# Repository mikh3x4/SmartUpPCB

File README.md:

this two may be needed to get submodule cloned

git submodule init
git submodule update

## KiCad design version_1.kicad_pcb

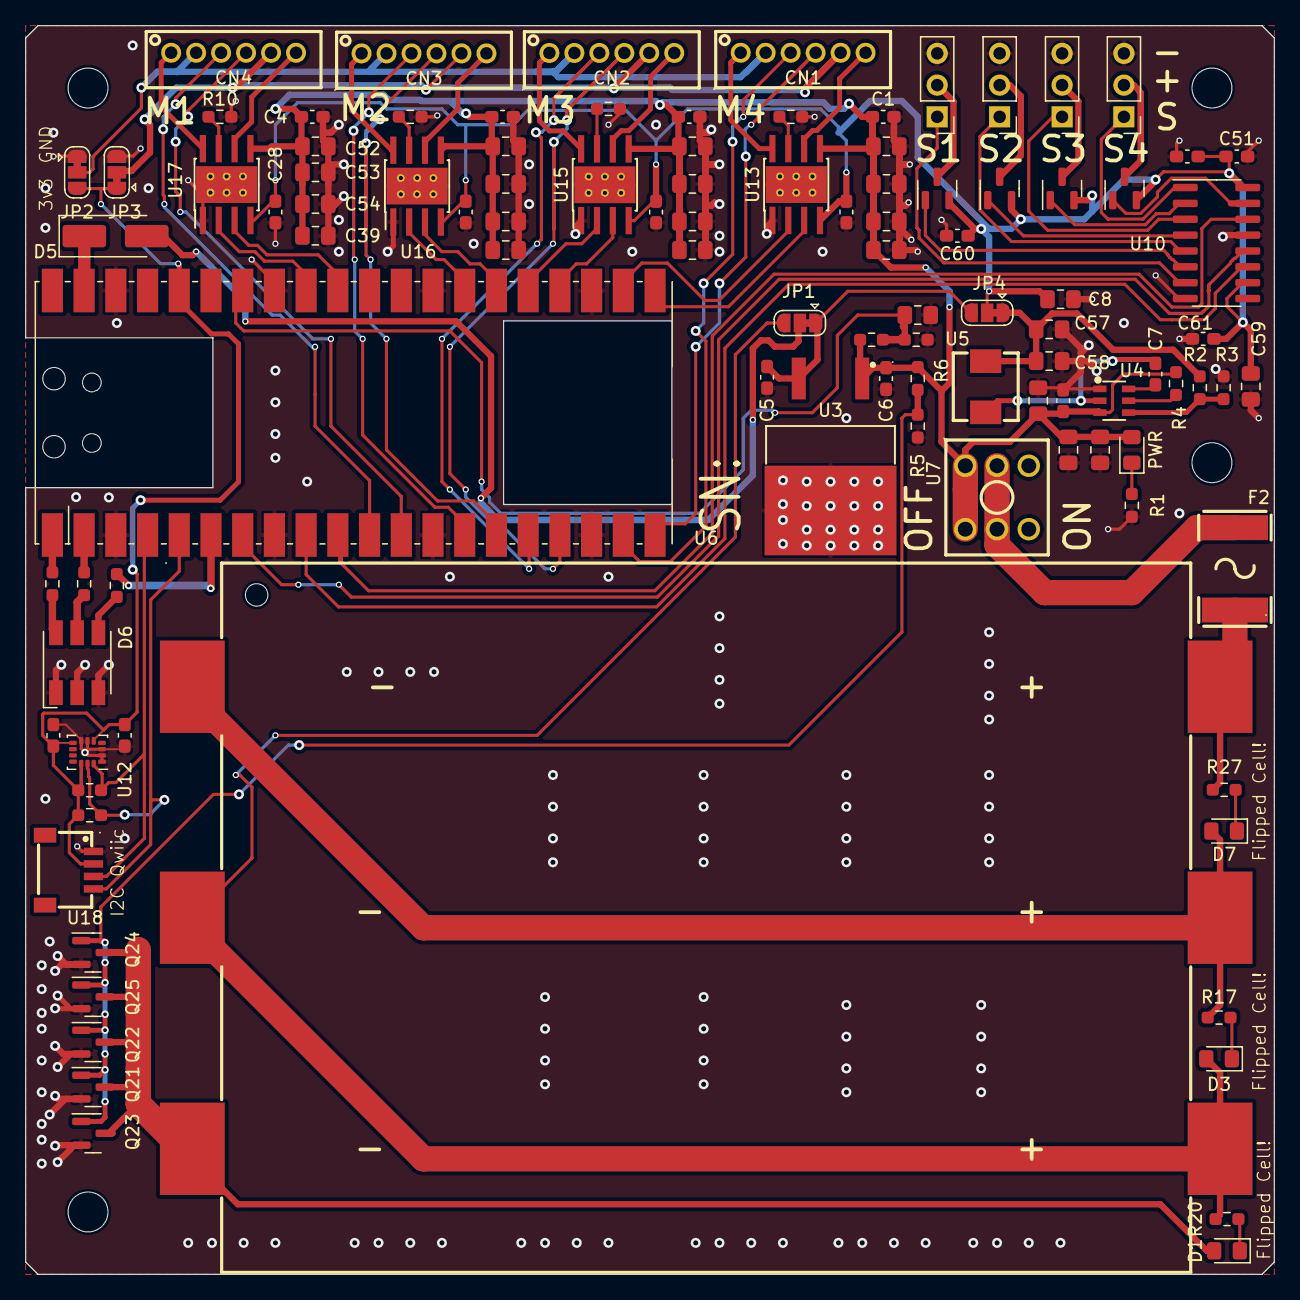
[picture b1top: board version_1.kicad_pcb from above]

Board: 4 copper layers, 100.0 x 100.0 mm, 107 parts (0 on the bottom side), 76 nets.

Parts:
C1, C2, C3, C4, C5, C7, C14, C16, C25, C26, C27, C28, C29, C50, C51, C60, C61: 100n; C_0603_1608Metric_Pad1.08x0.95mm_HandSolder
C6: 330n; C_0603_1608Metric_Pad1.08x0.95mm_HandSolder
C8, C11, C13, C15, C30, C31, C32, C33, C36, C37, C38, C39, C40, C41, C42, C45, C46, C47, C52, C53, C54, C57, C58, C59: 22u; C_0805_2012Metric_Pad1.18x1.45mm_HandSolder
CN1, CN2, CN3, CN4: B6B-PH-K-S(LF)(SN); CONN-TH_B6B-PH-K-S
D1, D3, D7: WRONG!; D_0805_2012Metric_Pad1.15x1.40mm_HandSolder
D4: PWR; D_0805_2012Metric_Pad1.15x1.40mm_HandSolder
D5: C145232; D_SMA_Handsoldering
D6: C2843868; LED_RGB_5050-6
F2: SMD2920B500TF; F2920
H1, H2, H3, H4: MountingHole; MountingHole_3.2mm_M3
JP1, JP2, JP3, JP4: Jumper_3_Bridged12; SolderJumper-3_P1.3mm_Bridged12_RoundedPad1.0x1.5mm
M5, M6, M7, M8: Motor_Servo_JR; PinHeader_1x03_P2.54mm_Vertical
Q17, Q18, Q19, Q20: AO3401A; SOT-23
Q21, Q22, Q23, Q24, Q25: AO3400A; SOT-23
R1, R21, R22, R23, R29, R30: 1k; R_0603_1608Metric_Pad0.98x0.95mm_HandSolder
R2: 56k; R_0603_1608Metric_Pad0.98x0.95mm_HandSolder
R3, R4, R25: 10k; R_0603_1608Metric_Pad0.98x0.95mm_HandSolder
R5, R6: 100k; R_0603_1608Metric_Pad0.98x0.95mm_HandSolder
R7, R8, R9, R10: 0.27; R_0603_1608Metric_Pad0.98x0.95mm_HandSolder
R17, R20, R27: 220; R_0603_1608Metric_Pad0.98x0.95mm_HandSolder
R26: 33k; R_0603_1608Metric_Pad0.98x0.95mm_HandSolder
U1: Pico; RPi_Pico_SMD_TH
U3: L7805CD2T-TR; TO-263-2_L10.0-W9.1-P5.08-LS15.2-TL
U4: TPS562209DDCR; SOT-23-6_L2.9-W1.6-P0.95-LS2.8-BL
U5: FXL0530-4R7-M; IND-SMD_L5.4-W5.2_FXL0530
U6: BH-18650-B5BA016; BAT-SMD_BH-18650-B5BA016
U7: 2AD1T1A2M2QES; SW-TH_2AD1T1A2M2QES
U10: 74HCT595D; SOP-16_3.9x9.9mm_P1.27mm
U12: C967633; LGA-14_3x2.5mm_P0.5mm_LayoutBorder3x4y
U13, U15, U16, U17: DRV8870DDA; Texas_HTSOP-8-1EP_3.9x4.9mm_P1.27mm_EP2.95x4.9mm_Mask2.4x3.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
U18: SM04B-SRSS-TB_(LF)(SN); CONN-SMD_4P-P1.00_SM04B-SRSS-TB-LF-SN

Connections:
1S: D3.2 (A), JP1.3 (B), R20.2, U6.3, U6.6
+3.3V: C16.1, C50.1, JP2.3 (B), JP3.1 (A), R29.1, R30.1, U1.36 (3V3), U12.5 (VDDIO), U12.8 (VDD), U12.12 (CS), U18.2
+5V: C8.1, C25.1, C26.1, C27.1, C28.1, C29.1, C51.1, C59.1, C60.1, C61.1, JP4.2 (C), Q17.2 (S), Q18.2 (S), Q19.2 (S), Q20.2 (S), U10.10 (~SRCLR), U10.16 (VCC), U13.4 (VREF), U15.4 (VREF), U16.4 (VREF), U17.4 (VREF)
/ENCODER1: CN1.3, U1.19 (GPIO14)
/ENCODER2: CN1.4, U1.20 (GPIO15)
/ENCODER3: CN2.3, U1.16 (GPIO12)
/ENCODER4: CN2.4, U1.17 (GPIO13)
/ENCODER5: CN3.3, U1.14 (GPIO10)
/ENCODER6: CN3.4, U1.15 (GPIO11)
/ENCODER7: CN4.3, U1.11 (GPIO8)
/ENCODER8: CN4.4, U1.12 (GPIO9)
/ML1: U1.21 (GPIO16), U13.3 (IN1)
/ML2: U1.24 (GPIO18), U15.3 (IN1)
/ML3: U1.26 (GPIO20), U16.3 (IN1)
/ML4: U1.31 (GPIO26_ADC0), U17.3 (IN1)
/MR1: U1.22 (GPIO17), U13.2 (IN2)
/MR2: U1.25 (GPIO19), U15.2 (IN2)
/MR3: U1.27 (GPIO21), U16.2 (IN2)
/MR4: U1.32 (GPIO27_ADC1), U17.2 (IN2)
/PWM_CLK: U1.9 (GPIO6), U10.11 (SRCLK)
/PWM_CS: U1.7 (GPIO5), U10.12 (RCLK)
/PWM_DATA: U1.10 (GPIO7), U10.14 (SER)
/SCL: R30.2, U1.5 (GPIO3), U12.13 (SCL), U18.4
/SDA: R29.2, U1.4 (GPIO2), U12.14 (SDA), U18.3
/Servo2/PWM: M7.1 (PWM), U10.3 (QD)
/Servo2/PWR: Q19.1 (G), U10.2 (QC)
/Servo/PWM: M8.1 (PWM), U10.1 (QB)
/Servo/PWR: Q20.1 (G), U10.15 (QA)
/Untitled Sheet4/PWM: M6.1 (PWM), U10.5 (QF)
/Untitled Sheet4/PWR: Q18.1 (G), U10.4 (QE)
/Untitled Sheet7/PWM: M5.1 (PWM), U10.7 (QH)
/Untitled Sheet7/PWR: Q17.1 (G), U10.6 (QG)
ENC_PWR_G: CN1.2, CN2.2, CN3.2, CN4.2, JP2.2 (C)
ENC_PWR_P: CN1.5, CN2.5, CN3.5, CN4.5, JP3.2 (C)
GND: C1.2, C2.2, C3.2, C4.2, C5.2, C6.2, C8.2, C11.2, C13.2, C14.2, C15.2, C16.2, C25.2, C26.2, C27.2, C28.2, C29.2, C30.2, C31.2, C32.2, C33.2, C36.2, C37.2, C38.2, C39.2, C40.2, C41.2, C42.2, C45.2, C46.2, C47.2, C50.2, C51.2, C52.2, C53.2, C54.2, C57.2, C58.2, C59.2, C60.2, C61.2, D6.1 (RK), D6.2 (GK), D6.3 (BK), JP2.1 (A), JP3.3 (B), M5.3 (-), M6.3 (-), M7.3 (-), M8.3 (-), Q21.2 (S), Q22.2 (S), Q23.2 (S), Q24.2 (S), Q25.2 (S), R1.1, R3.1, R5.1, R7.2, R8.2, R9.2, R10.2, R25.1, U1.3 (GND), U1.8 (GND), U1.13 (GND), U1.18 (GND), U1.23 (GND), U1.28 (GND), U1.33 (AGND), U1.38 (GND), U3.4 (GND), U4.1 (GND), U10.8 (GND), U10.13 (~OE), U12.1 (SDO/SA0), U12.2 (SDX), U12.3 (SCX), U12.6 (GND), U12.7 (GND), U13.1 (GND), U13.9 (GND), U15.1 (GND), U15.9 (GND), U16.1 (GND), U16.9 (GND), U17.1 (GND), U17.9 (GND), U18.1
Linear 5V: C5.1, JP1.1 (A), JP4.3 (B), U3.3 (OUT)
unnamed: D1.2 (A), Q21.3 (D), Q22.3 (D), Q23.3 (D), Q24.3 (D), Q25.3 (D), U6.5
unnamed: D1.1 (K), R20.1
unnamed: D3.1 (K), R17.1
unnamed: D4.1 (K), R1.2
unnamed: D5.2 (A), JP1.2 (C)
unnamed: D5.1 (K), U1.39 (VSYS)
unnamed: D6.4 (BA), R23.1
unnamed: D6.5 (GA), R22.1
unnamed: D6.6 (RA), R21.1
unnamed: D7.2 (A), R17.2, U6.1, U6.4
unnamed: D7.1 (K), R27.1
unnamed: F2.1, R27.2, U6.2
unnamed: F2.2, U7.2, U7.5
unnamed: C57.1, C58.1, JP4.1 (A), R2.2, U5.2
unnamed: M5.2 (+), Q17.3 (D)
unnamed: M6.2 (+), Q18.3 (D)
unnamed: M7.2 (+), Q19.3 (D)
unnamed: M8.2 (+), Q20.3 (D)
unnamed: Q21.1 (G), Q22.1 (G), Q23.1 (G), Q24.1 (G), Q25.1 (G), R5.2, R6.2
unnamed: R21.2, U1.1 (GPIO0)
unnamed: R22.2, U1.2 (GPIO1)
unnamed: R23.2, U1.6 (GPIO4)
unnamed: C15.1, R25.2, R26.2, U1.34 (GPIO28_ADC2)
unnamed: R4.1, U4.5 (EN)
unnamed: C7.1, U4.2 (SW), U5.1
unnamed: C7.2, U4.6 (VBST)
unnamed: R2.1, R3.2, U4.4 (VFB)
unnamed: R7.1, U13.7 (ISEN)
unnamed: CN1.6, U13.6 (OUT1)
unnamed: CN1.1, U13.8 (OUT2)
unnamed: R8.1, U15.7 (ISEN)
unnamed: CN2.6, U15.6 (OUT1)
unnamed: CN2.1, U15.8 (OUT2)
unnamed: R9.1, U16.7 (ISEN)
unnamed: CN3.6, U16.6 (OUT1)
unnamed: CN3.1, U16.8 (OUT2)
unnamed: R10.1, U17.7 (ISEN)
unnamed: CN4.6, U17.6 (OUT1)
unnamed: CN4.1, U17.8 (OUT2)
VCC: C1.1, C2.1, C3.1, C4.1, C6.1, C11.1, C13.1, C14.1, C30.1, C31.1, C32.1, C33.1, C36.1, C37.1, C38.1, C39.1, C40.1, C41.1, C42.1, C45.1, C46.1, C47.1, C52.1, C53.1, C54.1, D4.2 (A), R4.2, R6.1, R26.1, U3.1 (IN), U4.3 (VIN), U7.1, U7.4, U13.5 (VM), U15.5 (VM), U16.5 (VM), U17.5 (VM)

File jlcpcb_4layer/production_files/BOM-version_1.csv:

Comment,Designator,Footprint,LCSC
B6B-PH-K-S(LF)(SN),"CN1,CN2,CN3,CN4",CONN-TH_B6B-PH-K-S,C131342
C145232,D5,D_SMA_Handsoldering,C145232
L7805CD2T-TR,U3,TO-263-2_L10.0-W9.1-P5.08-LS15.2-TL,C15077
AO3401A,"Q17,Q18,Q19,Q20",SOT-23,C15127
SM04B-SRSS-TB_(LF)(SN),U18,CONN-SMD_4P-P1.00_SM04B-SRSS-TB-LF-SN,C160404
FXL0530-4R7-M,U5,IND-SMD_L5.4-W5.2_FXL0530,C177246
BH-18650-B5BA016,U6,BAT-SMD_BH-18650-B5BA016,C19184086
AO3400A,"Q21,Q22,Q23,Q24,Q25",SOT-23,C20917
PWR,D4,D_0805_2012Metric_Pad1.15x1.40mm_HandSolder,C2297
SMD2920B500TF,F2,F2920,C269189
74HCT595D,U10,SOP-16_3.9x9.9mm_P1.27mm,C282339
C2843868,D6,LED_RGB_5050-6,C2843868
Motor_Servo_JR,"M5,M6,M7,M8",PinHeader_1x03_P2.54mm_Vertical,C2935909
TPS562209DDCR,U4,SOT-23-6_L2.9-W1.6-P0.95-LS2.8-BL,C411814
2AD1T1A2M2QES,U7,SW-TH_2AD1T1A2M2QES,C496175
Pico,U1,RPi_Pico_SMD_TH,C7203003
WRONG!,"D1,D3,D7",D_0805_2012Metric_Pad1.15x1.40mm_HandSolder,C84256
DRV8870DDA,"U13,U15,U16,U17",Texas_HTSOP-8-1EP_3.9x4.9mm_P1.27mm_EP2.95x4.9mm_Mask2.4x3.1mm_ThermalVias,C86590
C967633,U12,LGA-14_3x2.5mm_P0.5mm_LayoutBorder3x4y,C967633
0.27,R9,R_0603_1608Metric_Pad0.98x0.95mm_HandSolder,
22u,C37,C_0805_2012Metric_Pad1.18x1.45mm_HandSolder,
100k,R5,R_0603_1608Metric_Pad0.98x0.95mm_HandSolder,
100n,C60,C_0603_1608Metric_Pad1.08x0.95mm_HandSolder,
220,R27,R_0603_1608Metric_Pad0.98x0.95mm_HandSolder,
Jumper_3_Bridged12,JP2,SolderJumper-3_P1.3mm_Bridged12_RoundedPad1.0x1.5mm,
Jumper_3_Bridged12,JP3,SolderJumper-3_P1.3mm_Bridged12_RoundedPad1.0x1.5mm,
22u,C30,C_0805_2012Metric_Pad1.18x1.45mm_HandSolder,
100n,C26,C_0603_1608Metric_Pad1.08x0.95mm_HandSolder,
Jumper_3_Bridged12,JP4,SolderJumper-3_P1.3mm_Bridged12_RoundedPad1.0x1.5mm,
10k,R25,R_0603_1608Metric_Pad0.98x0.95mm_HandSolder,
330n,C6,C_0603_1608Metric_Pad1.08x0.95mm_HandSolder,
100n,C7,C_0603_1608Metric_Pad1.08x0.95mm_HandSolder,
22u,C42,C_0805_2012Metric_Pad1.18x1.45mm_HandSolder,
1k,R29,R_0603_1608Metric_Pad0.98x0.95mm_HandSolder,
220,R17,R_0603_1608Metric_Pad0.98x0.95mm_HandSolder,
100n,C5,C_0603_1608Metric_Pad1.08x0.95mm_HandSolder,
100n,C50,C_0603_1608Metric_Pad1.08x0.95mm_HandSolder,
0.27,R8,R_0603_1608Metric_Pad0.98x0.95mm_HandSolder,
100k,R6,R_0603_1608Metric_Pad0.98x0.95mm_HandSolder,
22u,C11,C_0805_2012Metric_Pad1.18x1.45mm_HandSolder,
100n,C29,C_0603_1608Metric_Pad1.08x0.95mm_HandSolder,
100n,C28,C_0603_1608Metric_Pad1.08x0.95mm_HandSolder,
22u,C36,C_0805_2012Metric_Pad1.18x1.45mm_HandSolder,
MountingHole,H2,MountingHole_3.2mm_M3,
100n,C4,C_0603_1608Metric_Pad1.08x0.95mm_HandSolder,
1k,R23,R_0603_1608Metric_Pad0.98x0.95mm_HandSolder,
100n,C14,C_0603_1608Metric_Pad1.08x0.95mm_HandSolder,
100n,C3,C_0603_1608Metric_Pad1.08x0.95mm_HandSolder,
0.27,R7,R_0603_1608Metric_Pad0.98x0.95mm_HandSolder,
22u,C59,C_0805_2012Metric_Pad1.18x1.45mm_HandSolder,
22u,C39,C_0805_2012Metric_Pad1.18x1.45mm_HandSolder,
100n,C25,C_0603_1608Metric_Pad1.08x0.95mm_HandSolder,
100n,C2,C_0603_1608Metric_Pad1.08x0.95mm_HandSolder,
22u,C54,C_0805_2012Metric_Pad1.18x1.45mm_HandSolder,
22u,C13,C_0805_2012Metric_Pad1.18x1.45mm_HandSolder,
22u,C47,C_0805_2012Metric_Pad1.18x1.45mm_HandSolder,
220,R20,R_0603_1608Metric_Pad0.98x0.95mm_HandSolder,
0.27,R10,R_0603_1608Metric_Pad0.98x0.95mm_HandSolder,
22u,C38,C_0805_2012Metric_Pad1.18x1.45mm_HandSolder,
22u,C45,C_0805_2012Metric_Pad1.18x1.45mm_HandSolder,
22u,C46,C_0805_2012Metric_Pad1.18x1.45mm_HandSolder,
10k,R4,R_0603_1608Metric_Pad0.98x0.95mm_HandSolder,
33k,R26,R_0603_1608Metric_Pad0.98x0.95mm_HandSolder,
1k,R30,R_0603_1608Metric_Pad0.98x0.95mm_HandSolder,
1k,R21,R_0603_1608Metric_Pad0.98x0.95mm_HandSolder,
22u,C58,C_0805_2012Metric_Pad1.18x1.45mm_HandSolder,
100n,C1,C_0603_1608Metric_Pad1.08x0.95mm_HandSolder,
MountingHole,H1,MountingHole_3.2mm_M3,
22u,C15,C_0805_2012Metric_Pad1.18x1.45mm_HandSolder,
Jumper_3_Bridged12,JP1,SolderJumper-3_P1.3mm_Bridged12_RoundedPad1.0x1.5mm,
100n,C61,C_0603_1608Metric_Pad1.08x0.95mm_HandSolder,
22u,C8,C_0805_2012Metric_Pad1.18x1.45mm_HandSolder,
100n,C27,C_0603_1608Metric_Pad1.08x0.95mm_HandSolder,
22u,C52,C_0805_2012Metric_Pad1.18x1.45mm_HandSolder,
100n,C16,C_0603_1608Metric_Pad1.08x0.95mm_HandSolder,
10k,R3,R_0603_1608Metric_Pad0.98x0.95mm_HandSolder,
22u,C31,C_0805_2012Metric_Pad1.18x1.45mm_HandSolder,
22u,C57,C_0805_2012Metric_Pad1.18x1.45mm_HandSolder,
MountingHole,H4,MountingHole_3.2mm_M3,
22u,C53,C_0805_2012Metric_Pad1.18x1.45mm_HandSolder,
22u,C32,C_0805_2012Metric_Pad1.18x1.45mm_HandSolder,
MountingHole,H3,MountingHole_3.2mm_M3,
22u,C41,C_0805_2012Metric_Pad1.18x1.45mm_HandSolder,
22u,C40,C_0805_2012Metric_Pad1.18x1.45mm_HandSolder,
100n,C51,C_0603_1608Metric_Pad1.08x0.95mm_HandSolder,
1k,R1,R_0603_1608Metric_Pad0.98x0.95mm_HandSolder,
22u,C33,C_0805_2012Metric_Pad1.18x1.45mm_HandSolder,
56k,R2,R_0603_1608Metric_Pad0.98x0.95mm_HandSolder,
1k,R22,R_0603_1608Metric_Pad0.98x0.95mm_HandSolder,

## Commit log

2023-05-24 slowly drafting all requirements
2023-05-25 initial schematic of output section
2023-05-25 mostek H, serva, SMPS
2023-05-25 H bridge, 5V SMPS, servo driver
2023-06-06 routing of H bridges and servo power pins
2023-06-06 footprint for 18650 holder example pcb battery layout
2023-06-15 added pico model as submodule
2023-06-16 more capacitance near motors 16x22uF total 3S->2S
2023-06-17 verison 1.0 just routed
2023-06-18 version 1.1 item colisions fixed added silkscreen DRC done
2023-06-18 cat added
2023-06-19 new version of layout with diodes improved power routing a little bit
2023-06-19 placement files
2023-06-20 najnowsza wersja
2024-05-23 jlcpcb part numbs
2024-05-23 added gitignore
2024-05-28 added moany componaets
2024-05-28 some changes
2024-05-28 specified correct shift register
2024-05-29 added more symbols
2024-05-29 removed all dc to dc
2024-05-29 Added thing for servo pwoer
2024-05-29 encoder power fliping
2024-05-29 big layout changes
2024-05-29 clean up
2024-05-29 fliped servo mosfets
2024-05-30 new servo routing
2024-05-30 squish
2024-05-30 clean up2
2024-05-31 tetris
2024-05-31 cleanup
2024-05-31 delt with errors
2024-05-31 wearninigs
2024-05-31 mostly done
2024-05-31 exported
2024-05-31 new libs
2024-05-31 jlc export
2024-06-06 4 layer
2024-06-06 as ordered
